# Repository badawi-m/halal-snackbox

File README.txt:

# halalsnackbox

Based on the excellent [Flatbox project by jfedor2](https://github.com/jfedor2/flatbox), `halalsnackbox` is:
* fully custom PCB inspired by [rev5](https://github.com/jfedor2/flatbox/tree/master/hardware-rev5)
* support for gateron low-profile switches
* additional keys for shift and w

## Installation

* Clone repository
* Open `flatbox-halal-low-prof/flatbox-halal-low-prof.kicad_pro`

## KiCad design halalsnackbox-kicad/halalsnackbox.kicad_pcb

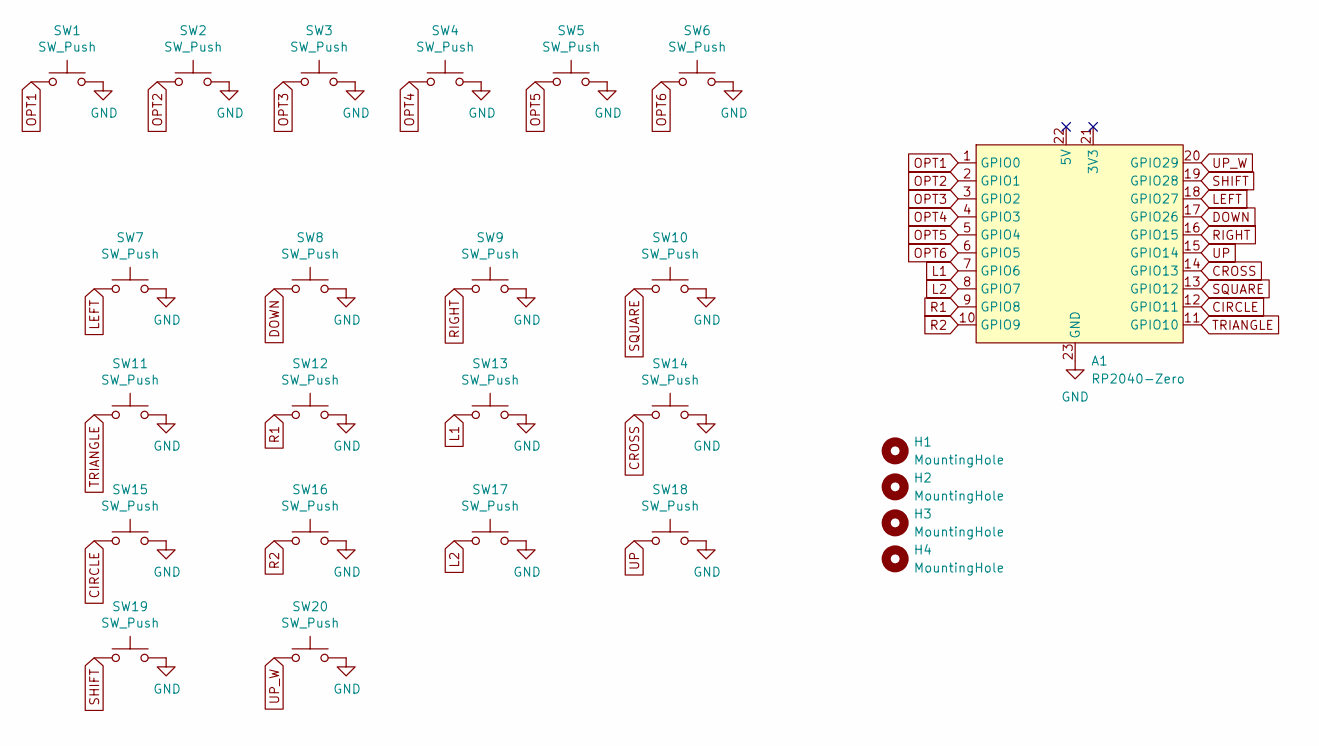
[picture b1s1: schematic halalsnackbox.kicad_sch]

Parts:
A1: RP2040-Zero
H1, H2, H3, H4: MountingHole; MountingHole_6.4mm_M6
SW1, SW2, SW3, SW4, SW5, SW6: SW_Push; SW_PUSH_6mm_H9.5mm
SW7, SW8, SW9, SW10, SW11, SW12, SW13, SW14, SW15, SW16, SW17, SW18, SW19, SW20: SW_Push; SW_Gateron_LowProfile_HotSwap_THT

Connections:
CIRCLE: A1.12 (GPIO11), SW15.1
CROSS: A1.14 (GPIO13), SW14.1
DOWN: A1.17 (GPIO26), SW8.1
GND: A1.23 (GND), SW1.2, SW2.2, SW3.2, SW4.2, SW5.2, SW6.2, SW7.2, SW8.2, SW9.2, SW10.2, SW11.2, SW12.2, SW13.2, SW14.2, SW15.2, SW16.2, SW17.2, SW18.2, SW19.2, SW20.2
L1: A1.7 (GPIO6), SW13.1
L2: A1.8 (GPIO7), SW17.1
LEFT: A1.18 (GPIO27), SW7.1
OPT1: A1.1 (GPIO0), SW1.1
OPT2: A1.2 (GPIO1), SW2.1
OPT3: A1.3 (GPIO2), SW3.1
OPT4: A1.4 (GPIO3), SW4.1
OPT5: A1.5 (GPIO4), SW5.1
OPT6: A1.6 (GPIO5), SW6.1
R1: A1.9 (GPIO8), SW12.1
R2: A1.10 (GPIO9), SW16.1
RIGHT: A1.16 (GPIO15), SW9.1
SHIFT: A1.19 (GPIO28), SW19.1
SQUARE: A1.13 (GPIO12), SW10.1
TRIANGLE: A1.11 (GPIO10), SW11.1
UP: A1.15 (GPIO14), SW18.1
UP_W: A1.20 (GPIO29), SW20.1

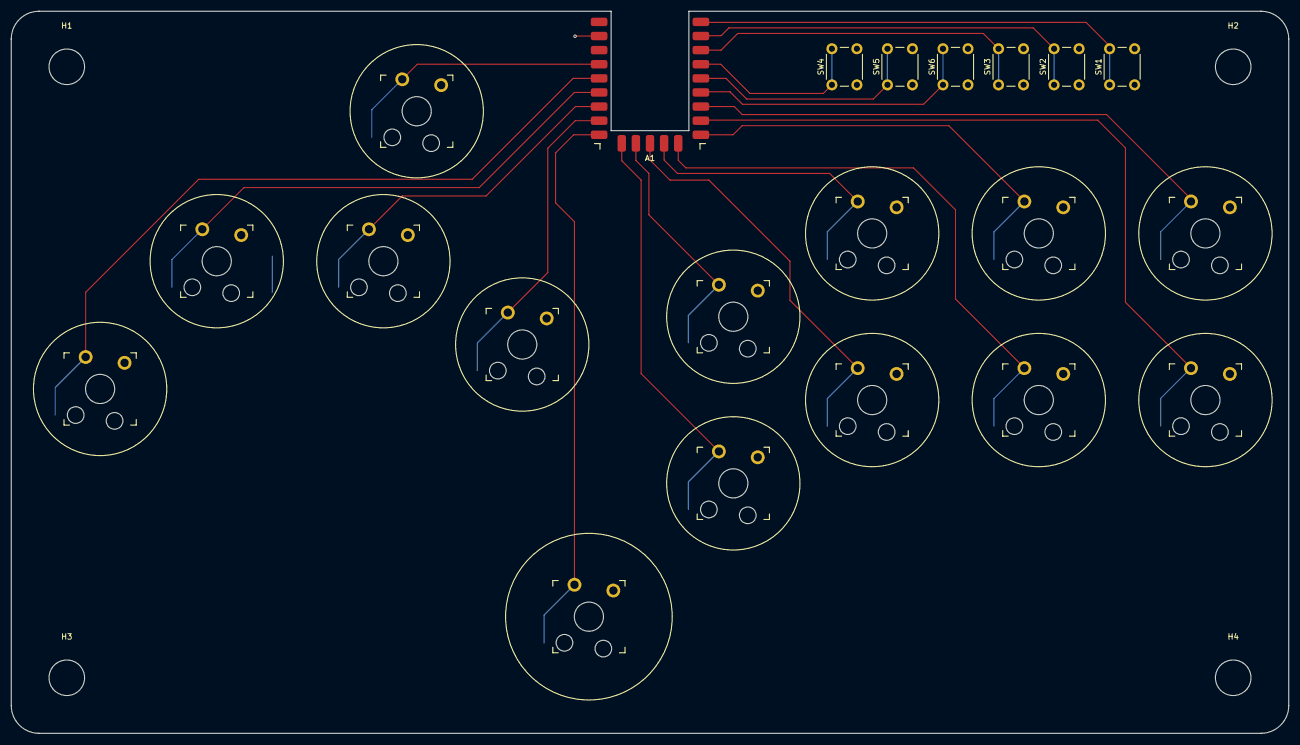
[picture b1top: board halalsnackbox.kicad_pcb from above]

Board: 2 copper layers, 230.0 x 130.0 mm, 25 parts (0 on the bottom side), 21 nets.

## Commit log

2024-03-11 ïnitial commit
2024-03-12 Fix Readme format
2024-03-14 added 3d model for rp2040, gateron switch and hotswap socket
2024-03-14 cleaned up signal trace
2024-03-17 revised kicad project file structure
2024-03-17 Modified file structure
2024-03-17 Added freecad file for 3d printed case
2024-03-18 updated 3d case file
2024-07-29 generate gerber for manufacturing
2024-09-10 WIP: case
